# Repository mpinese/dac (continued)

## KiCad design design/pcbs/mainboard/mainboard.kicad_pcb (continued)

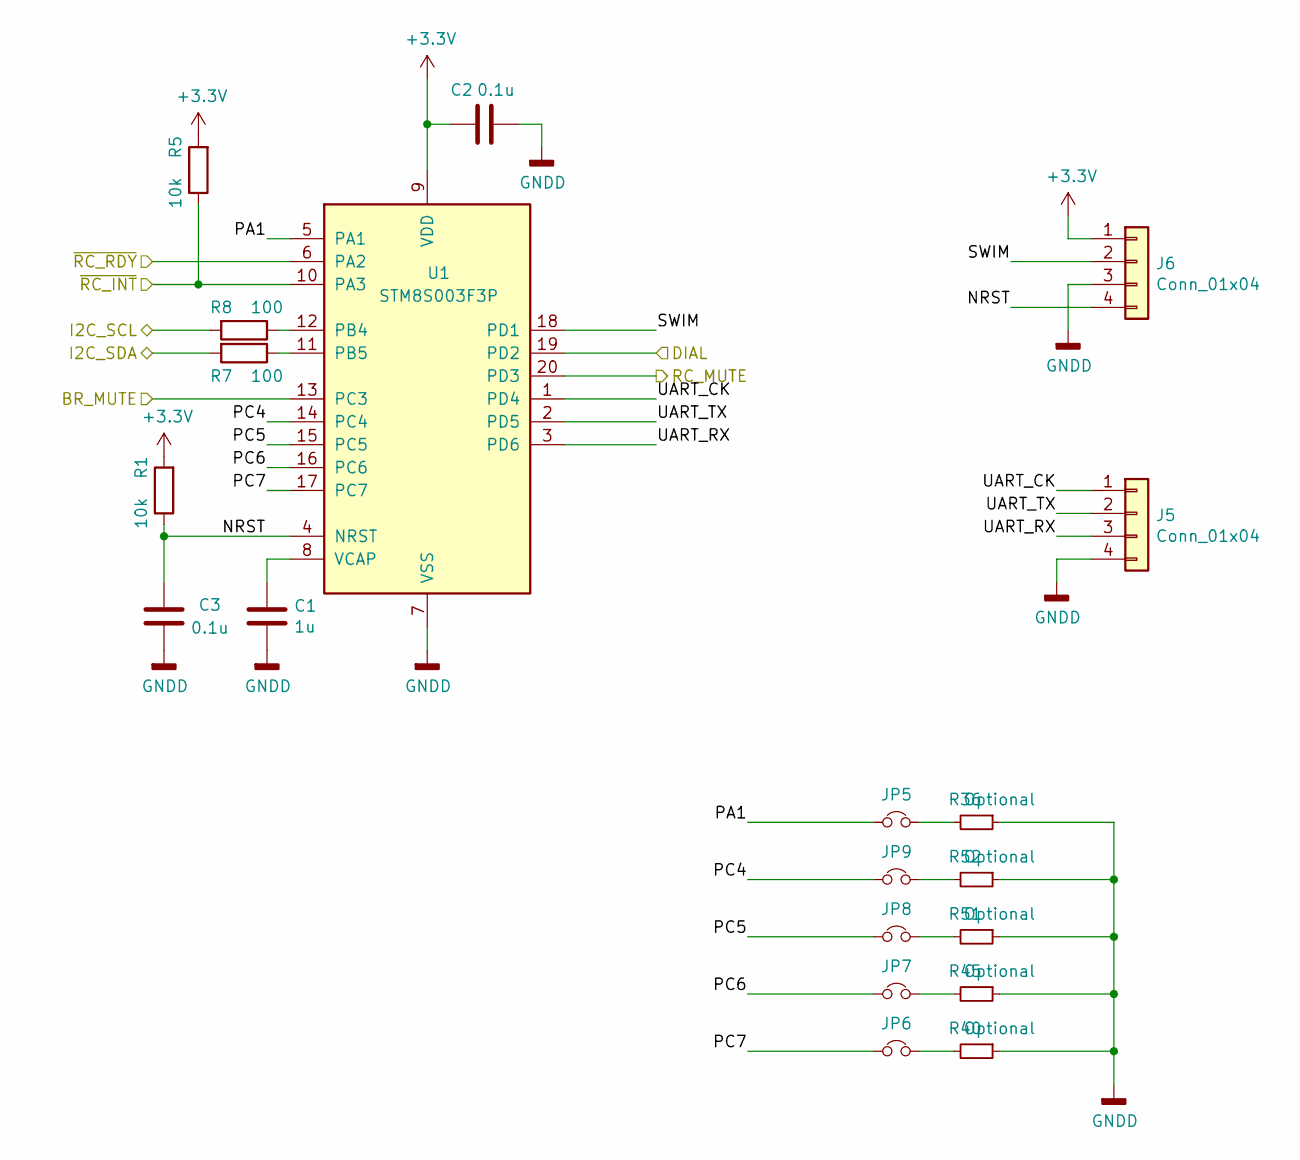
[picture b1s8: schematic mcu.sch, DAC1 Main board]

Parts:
C1: 1u; C_0805_2012Metric; LCSC C28323
C2, C3: 0.1u; C_0603_1608Metric; LCSC C14663
J5, J6: Conn_01x04; PinHeader_1x04_P2.54mm_Vertical
JP5, JP6, JP7, JP8, JP9: PinHeader_1x02_P2.54mm_Vertical
R1, R5: 10k; R_0402_1005Metric; LCSC C25744
R7, R8: 100; R_0402_1005Metric; LCSC C25076
R36, R40, R45, R51, R52: Optional; R_Axial_DIN0204_L3.6mm_D1.6mm_P5.08mm_Horizontal
U1: STM8S003F3P; TSSOP-20_4.4x6.5mm_P0.65mm; LCSC C52717

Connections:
/ASRC/I2C_SCL: R8.2; also elsewhere on the board
/ASRC/I2C_SDA: R7.2; also elsewhere on the board
/ASRC/MUTE: U1.20 (PD3); also elsewhere on the board
/ASRC/~INT: R5.1, U1.10 (PA3); also elsewhere on the board
/MCU/BR_MUTE: U1.13 (PC3); also elsewhere on the board
/MCU/DIAL: U1.19 (PD2); also elsewhere on the board
/MCU/NRST: C3.1, J6.4, R1.1, U1.4 (NRST)
/MCU/PA1: JP5.1, U1.5 (PA1)
/MCU/PC4: JP9.1, U1.14 (PC4)
/MCU/PC5: JP8.1, U1.15 (PC5)
/MCU/PC6: JP7.1, U1.16 (PC6)
/MCU/PC7: JP6.1, U1.17 (PC7)
/MCU/SWIM: J6.2, U1.18 (PD1)
/MCU/UART_CK: J5.1, U1.1 (PD4)
/MCU/UART_RX: J5.3, U1.3 (PD6)
/MCU/UART_TX: J5.2, U1.2 (PD5)
/MCU/~RC_RDY: U1.6 (PA2); also elsewhere on the board
GNDD: C1.2, C2.2, C3.2, J5.4, J6.3, R36.1, R40.1, R45.1, R51.1, R52.1, U1.7 (VSS); also elsewhere on the board
unnamed: C1.1, U1.8 (VCAP)
unnamed: JP5.2, R36.2
unnamed: JP6.2, R40.2
unnamed: JP7.2, R45.2
unnamed: JP8.2, R51.2
unnamed: JP9.2, R52.2
unnamed: R7.1, U1.11 (PB5)
unnamed: R8.1, U1.12 (PB4)

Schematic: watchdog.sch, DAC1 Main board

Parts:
C40, C82: 22u; C_0805_2012Metric; LCSC C45783
D2, D3, D6, D7: 5V6; D_MiniMELF; LCSC C8062
D4, D5: D; D_SOD-123F; LCSC C64898
K3, K4: EC2-12NU; RELAY_EC2-5NU; DigiKey 399-11029-5-ND
Q1, Q2, Q4, Q5, Q6, Q7, Q8, Q9, Q11, Q12: SS8050; SOT-23; LCSC C2150
Q3, Q10: SS8550; SOT-23; LCSC C8542
R11, R13, R72, R74: 2.2k; R_0402_1005Metric; LCSC C25879
R12, R14, R68, R69: 5.6k; R_0402_1005Metric; LCSC C25908
R20, R73: 15k; R_0402_1005Metric; LCSC C25756
R21, R71: 10k; R_0402_1005Metric; LCSC C25744
R31, R63: 22k; R_0402_1005Metric; LCSC C25768

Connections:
+10V: D4.1 (K), K3.1, R11.1, R20.1, R31.2; also elsewhere on the board
+10V_AMP: D5.1 (K), K4.1, R63.2, R73.1, R74.1; also elsewhere on the board
-10V: C40.2, Q2.2 (E), Q4.2 (E), Q5.2 (E), R14.2; also elsewhere on the board
-10V_AMP: C82.2, Q8.2 (E), Q9.2 (E), Q11.2 (E), R68.2; also elsewhere on the board
/Headphone Amp/LOUT: K4.4; also elsewhere on the board
/Headphone Amp/ROUT: K4.9; also elsewhere on the board
/LOUT: K3.4; also elsewhere on the board
/ROUT: K3.9; also elsewhere on the board
GND_AMP: K4.3, K4.10, Q7.2 (E), Q10.1 (B), Q12.2 (E), R69.2, R71.1, R72.1; also elsewhere on the board
unnamed: C40.1, Q4.3 (C), Q5.3 (C), Q6.1 (B), R31.1
unnamed: C82.1, Q7.1 (B), Q8.3 (C), Q9.3 (C), R63.1
unnamed: D2.1 (K), R11.2, R12.1
unnamed: D2.2 (A), Q1.1 (B)
unnamed: D3.1 (K), R13.2, R14.1
unnamed: D3.2 (A), Q2.1 (B)
unnamed: D4.2 (A), K3.12, Q6.3 (C)
unnamed: D5.2 (A), K4.12, Q7.3 (C)
unnamed: D6.1 (K), R68.1, R72.2
unnamed: D6.2 (A), Q11.1 (B)
unnamed: D7.1 (K), R69.1, R74.2
unnamed: D7.2 (A), Q12.1 (B)
unnamed: Q1.3 (C), Q3.2 (E), R20.2
unnamed: Q2.3 (C), Q4.1 (B), R21.2
unnamed: Q3.3 (C), Q5.1 (B)
unnamed: Q10.2 (E), Q12.3 (C), R73.2
unnamed: Q8.1 (B), Q10.3 (C)
unnamed: Q9.1 (B), Q11.3 (C), R71.2

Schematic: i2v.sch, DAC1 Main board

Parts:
C23, C36, C50, C52, C62, C70: 10u; CP_EIA-3216-18_Kemet-A; LCSC C7171
C24, C47, C53, C69: 430p; C_0603_1608Metric; DigiKey 399-15401-1-ND
C26, C41, C46, C57, C58, C68: 0.1u; C_0603_1608Metric; LCSC C14663
C37, C38, C65, C66: 1.2n; C_0603_1608Metric; DigiKey 399-14950-1-ND
R27, R35, R43, R53: 820; R_0603_1608Metric; DigiKey RG16N820WCT-ND
R28, R30, R48, R50: 1k; R_0603_1608Metric; DigiKey RG16N1.0KWCT-ND
R33, R34, R46, R47: 270; R_0603_1608Metric; DigiKey RG16N270WCT-ND
R38, R42: 25; R_0603_1608Metric; DigiKey 764-1409-1-ND
U9, U13, U15: OPA1612AxD; SOIC-8_3.9x4.9mm_P1.27mm; DigiKey 296-39098-1-ND

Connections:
+10V: C23.1, C26.1, C36.1, C46.1, C52.1, C58.1, U9.8 (V+), U13.8 (V+), U15.8 (V+); also elsewhere on the board
-10V: C41.2, C50.2, C57.2, C62.2, C68.2, C70.2, U9.4 (V-), U13.4 (V-), U15.4 (V-); also elsewhere on the board
/DAC/I2V/IIN+L: C53.1, R43.2, U15.6 (-); also elsewhere on the board
/DAC/I2V/IIN+R: C24.1, R27.2, U9.6 (-); also elsewhere on the board
/DAC/I2V/IIN-L: C69.1, R53.2, U15.2 (-); also elsewhere on the board
/DAC/I2V/IIN-R: C47.1, R35.2, U9.2 (-); also elsewhere on the board
/LOUT: R42.1; also elsewhere on the board
/ROUT: R38.1; also elsewhere on the board
unnamed: C24.2, R27.1, R28.2, U9.7
unnamed: C37.1, R33.2, R38.2, U13.7
unnamed: C37.2, R30.1, R33.1, U13.6 (-)
unnamed: C38.1, R28.1, R34.2, U13.5 (+)
unnamed: C47.2, R30.2, R35.1, U9.1
unnamed: C53.2, R43.1, R48.2, U15.7
unnamed: C65.1, R42.2, R46.2, U13.1
unnamed: C65.2, R46.1, R50.1, U13.2 (-)
unnamed: C66.1, R47.2, R48.1, U13.3 (+)
unnamed: C69.2, R50.2, R53.1, U15.1

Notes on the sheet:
Equations defining behaviour: R1: TIA feedback R2: DA series R3: DA feedback C1: TIA feedback C3: DA feedback (1) R1*(6.2+7.8/2)*1e-3 <= 10-1 (1 V headroom w/ 10 V rail) (2) R3/R2*R1*7.8*1e-3 <= 3.472/2 (Line out level) (3) R3/R2 is minimised (Minimise noise gain) (4) 3.472 - R3/R2*R1*7.8*1e-3 is m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
TINA-TI simulations:
Phase margin 57 deg @ 37 MHz:
Group delay flat to 20 kHz:
Gain flat to 20 kHz:
Noise 700 nV RMS up to 20 kHz
In THD+N terms this noise is 0.000057% relative to a 1.228 V RMS full scale.

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
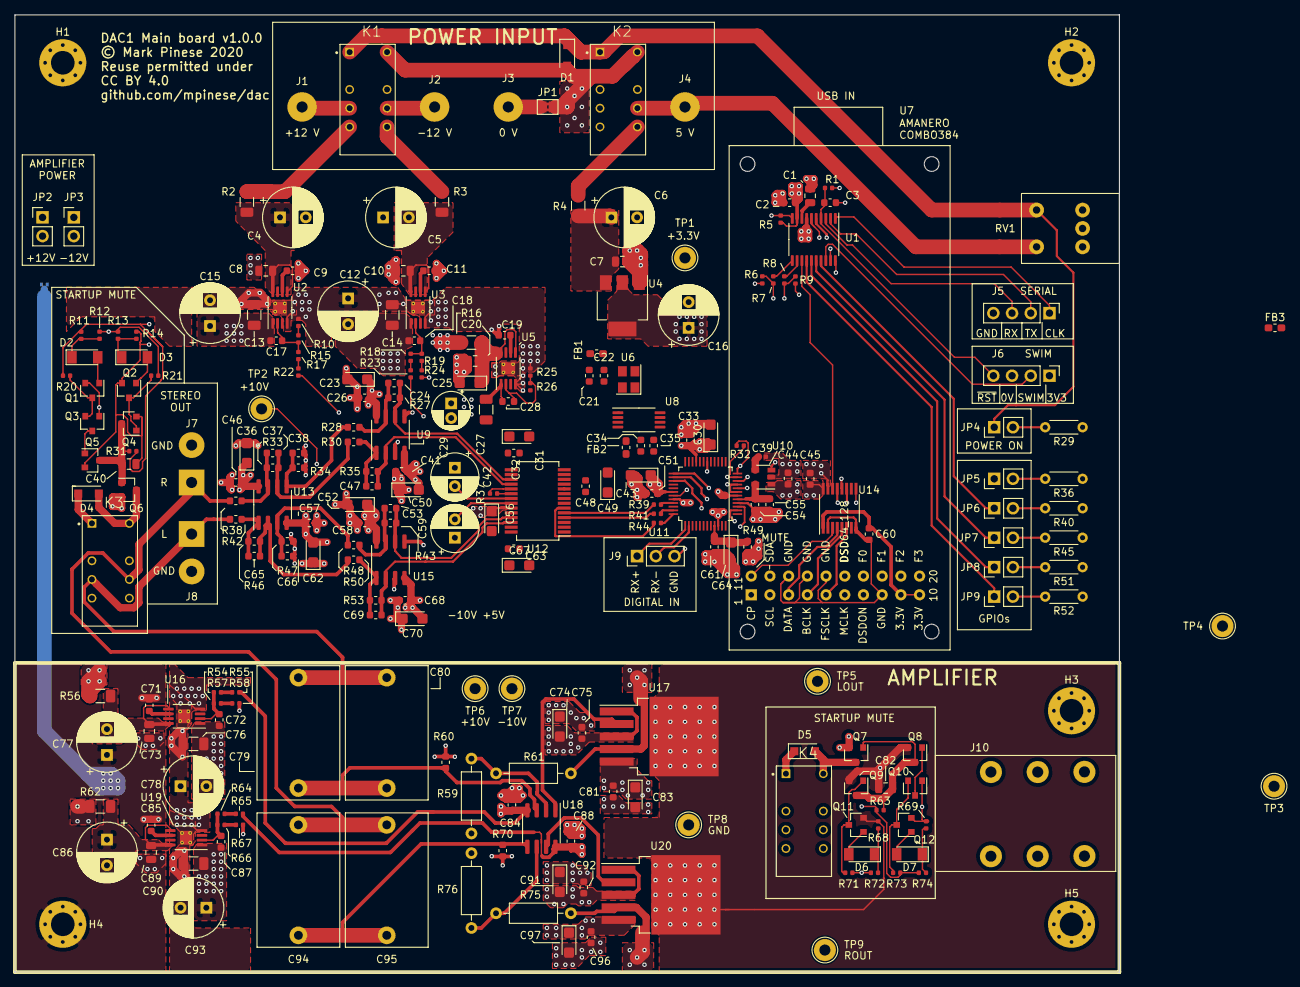
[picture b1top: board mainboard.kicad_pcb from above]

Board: 4 copper layers, 150.0 x 130.0 mm, 254 parts (1 on the bottom side), 139 nets.

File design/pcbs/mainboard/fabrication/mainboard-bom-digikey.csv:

Comment,Designator,Footprint,DigiKey,Quantity
KC3225K24.5760C1GE00,U6,Crystal:Crystal_SMD_3225-4Pin_3.2x2.5mm,1253-1407-1-ND,1
100u,C16,Capacitor_THT:CP_Radial_D8.0mm_P3.50mm,1572-1662-ND,1
TPS79318-EP,U10,Package_TO_SOT_SMD:SOT-23-5,296-12155-1-ND,1
SRC4392,U11,Package_QFP:TQFP-48_7x7mm_P0.5mm,296-19740-1-ND,1
PCM1792A,U12,Package_SO:SSOP-28_5.3x10.2mm_P0.65mm,296-26303-5-ND,1
TPS7A30,"U3,U16",Package_SO:MSOP-8-1EP_3x3mm_P0.65mm_EP1.68x1.88mm_ThermalVias,296-27750-1-ND,2
TPS7A49,"U2,U19,U5",Package_SO:MSOP-8-1EP_3x3mm_P0.65mm_EP1.68x1.88mm_ThermalVias,296-27751-1-ND,3
TLV1117-33,U4,Package_TO_SOT_SMD:SOT-223-3_TabPin2,296-28778-1-ND,1
OPA1612AxD,"U18,U15,U9,U13",Package_SO:SOIC-8_3.9x4.9mm_P1.27mm,296-39098-1-ND,4
LME49600,"U17,U20",Package_TO_SOT_SMD:TO-263-5_TabPin3,296-43968-5-ND,2
Si8645BA-B-IU,U14,Package_SO:QSOP-16_3.9x4.9mm_P0.635mm,336-2096-5-ND,1
EC2-12NU,"K3,K4",RELAY_EC2-5NU,399-11029-5-ND,2
EC2-5NU,"K1,K2",mainboard:RELAY_EC2-5NU,399-11052-5-ND,2
1.2n,"C37,C38,C65,C66",Capacitor_SMD:C_0603_1608Metric,399-14950-1-ND,4
430p,"C47,C24,C69,C53",Capacitor_SMD:C_0603_1608Metric,399-15401-1-ND,4
4.7,R49,Resistor_SMD:R_0603_1608Metric,408-1436-1-ND,1
2.2u,"C80,C79,C94,C95",Capacitor_THT:C_Rect_L18.0mm_W11.0mm_P15.00mm_FKS3_FKP3,732-11840-ND,4
47u,"C15,C12,C4,C5,C93,C78,C86,C77,C6",Capacitor_THT:CP_Radial_D8.0mm_P3.50mm,732-6324-1-ND,9
47u,"C42,C59,C29",Capacitor_THT:CP_Radial_D5.0mm_P2.00mm,732-9306-1-ND,3
25,"R38,R42",Resistor_SMD:R_0603_1608Metric,764-1409-1-ND,2
5PB1102,U8,Package_SO:TSSOP-8_4.4x3mm_P0.65mm,800-2889-5-ND,1
AudioJackSw,J10,mainboard:Amphenol_ACJS-MHOM,889-1818-ND,1
P091S-FC20BR10K,RV1,mainboard:P091S-FC20BR10K,987-1283-ND,1
1k,"R30,R28,R50,R48",Resistor_SMD:R_0603_1608Metric,RG16N1.0KWCT-ND,4
270,"R33,R34,R46,R47",Resistor_SMD:R_0603_1608Metric,RG16N270WCT-ND,4
820,"R35,R27,R53,R43",Resistor_SMD:R_0603_1608Metric,RG16N820WCT-ND,4
4.7k,"R60,R70",Resistor_SMD:R_0603_1608Metric,RG16P4.7KBCT-ND,2
Conn_Coaxial,"J7,J8",Connector_Wire:SolderWirePad_1x02_P5.08mm_Drill1.5mm,SC1828-ND,2
XLR5,#J3,,IO-XLR5-M-EV,1

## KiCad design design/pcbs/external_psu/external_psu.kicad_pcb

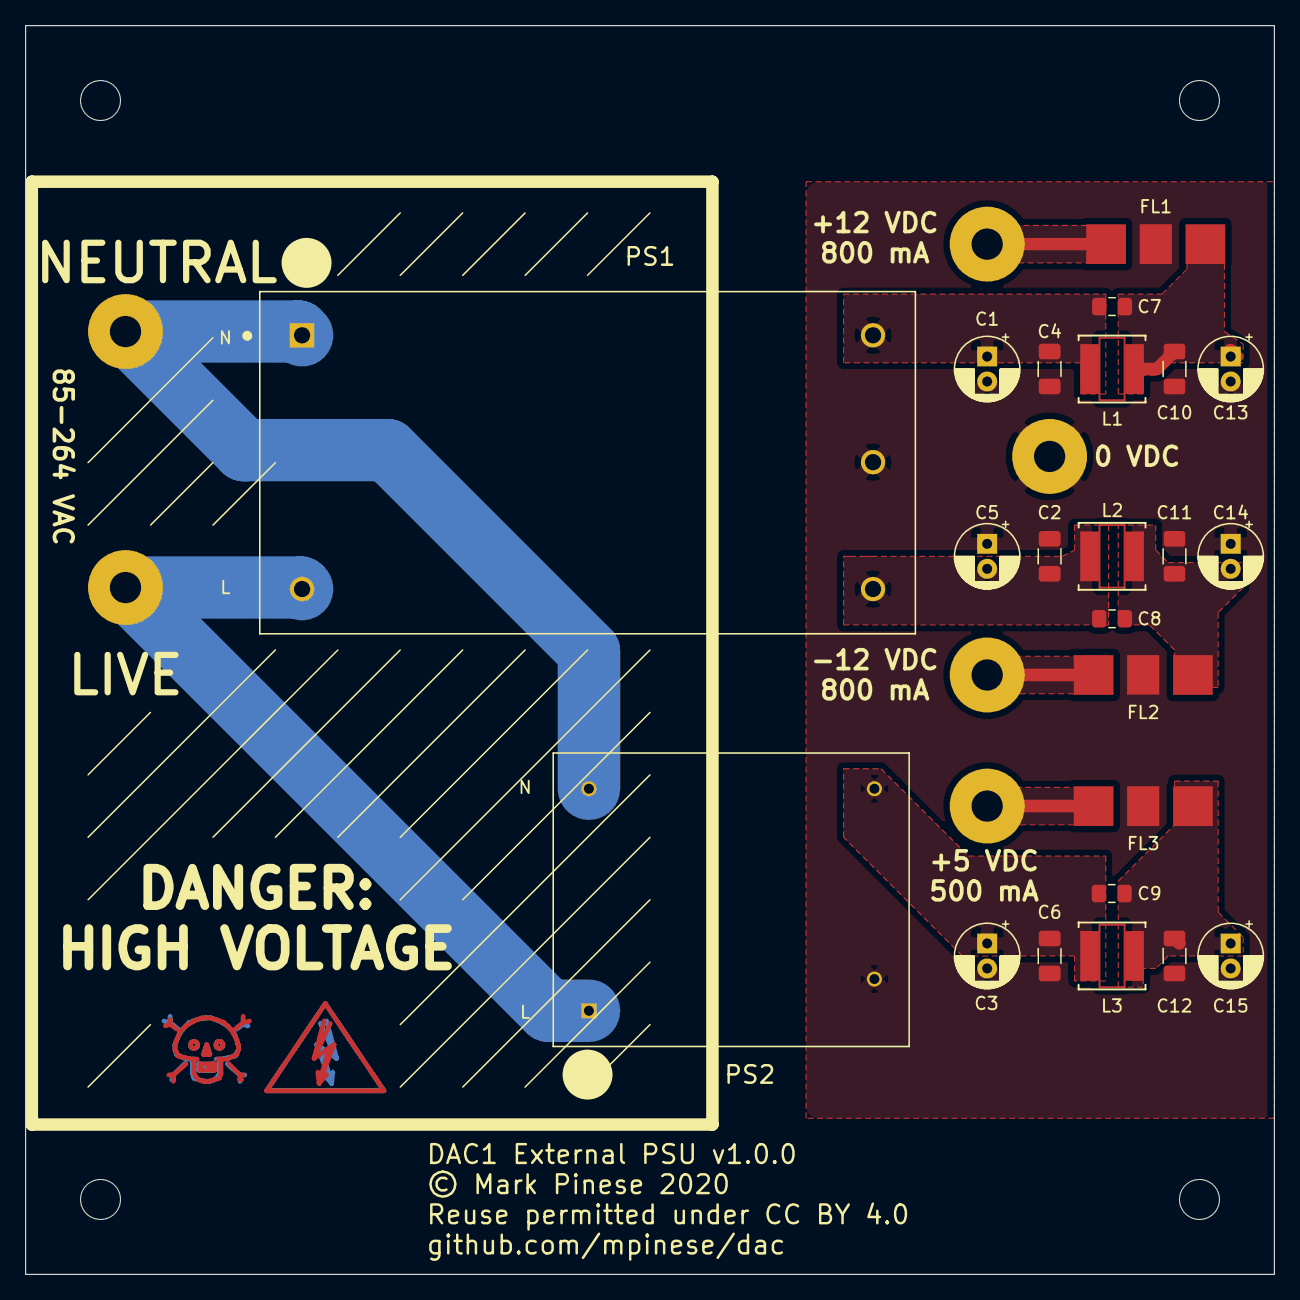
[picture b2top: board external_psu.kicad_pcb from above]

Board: 2 copper layers, 100.0 x 100.0 mm, 33 parts (0 on the bottom side), 12 nets.

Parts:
C1, C2, C3, C13, C14, C15: 6.8u; CP_Radial_D5.0mm_P2.00mm
C4, C5, C6, C10, C11, C12: 2.2u; C_1206_3216Metric
C7, C8, C9: 15n; C_0805_2012Metric_Pad1.15x1.40mm_HandSolder
CONN1: L; SolderWirePad_1x01_Drill2.5mm
CONN2: N; SolderWirePad_1x01_Drill2.5mm
CONN3: +12V; SolderWirePad_1x01_Drill2.5mm
CONN4: 0V; SolderWirePad_1x01_Drill2.5mm
CONN5: -12V; SolderWirePad_1x01_Drill2.5mm
CONN6: +5V; SolderWirePad_1x01_Drill2.5mm
FL1, FL2, FL3: EMI_Filter_CLC; 4700-008MLF
H1, H2, H3, H4: MountingHole; MountingHole_3.2mm_M3
L1, L2, L3: 15u; NRS5020T150MMGJ
PS1: RAC20-12DK; CONV_RAC20-12DK
PS2: RAC03-05SK; CONV_RAC03-05SK

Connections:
/LIVE: CONN1.1, PS1.2, PS2.1
/NEUTRAL: CONN2.1, PS1.1, PS2.4
GND: C1.2, C2.1, C3.2, C4.2, C5.2, C6.2, C10.2, C11.2, C12.2, C13.2, C14.1, C15.2, CONN4.1, FL1.2, FL2.2, FL3.2, PS1.4, PS2.2
unnamed: C1.1, C4.1, C7.1, L1.1, PS1.5
unnamed: C2.2, C5.1, C8.1, L2.1, PS1.3
unnamed: C3.1, C6.1, C9.1, L3.1, PS2.3
unnamed: C7.2, C10.1, C13.1, FL1.1, L1.2
unnamed: C8.2, C11.1, C14.2, FL2.1, L2.2
unnamed: C9.2, C12.1, C15.1, FL3.1, L3.2
unnamed: CONN3.1, FL1.3
unnamed: CONN5.1, FL2.3
unnamed: CONN6.1, FL3.3

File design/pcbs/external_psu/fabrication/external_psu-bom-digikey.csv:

Comment,Designator,Footprint, DigiKey,Quantity
6.8u,"C1,C13,C2,C14,C3,C15",Capacitor_THT:CP_Radial_D5.0mm_P2.00mm,565-4006-ND,6
2.2u,"C4,C10,C5,C11,C6,C12",Capacitor_SMD:C_1206_3216Metric,1276-3137-1-ND,6
15n,"C7,C8,C9",Capacitor_SMD:C_0805_2012Metric_Pad1.15x1.40mm_HandSolder,732-12189-1-ND,3
~,#FB1,,240-2497-ND,1
EMI_Filter_CLC,"FL1,FL2,FL3",dac:4700-008MLF,410-1196-1-ND,3
15u,"L1,L2,L3",dac:NRS5020T150MMGJ,587-2410-1-ND,3
RAC20-12DK,PS1,CONV_RAC20-12DK,945-3239-ND,1
RAC03-05SK,PS2,CONV_RAC03-05SK,945-3441-ND,1
IEC 320-C14 socket,#J1,,Q334-ND ,1
XLR5,#J2,,1937-1035-ND,1

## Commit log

2020-06-25 Initial commit.
2020-06-27 Added jitter simulation that supports the use of a 5 ps RMS jitter oscillator.
2020-06-27 Completed layout of main board, cleaned up some libraries.
2020-06-27 Fixed mounting hole alignment
2020-06-27 Tweaked silkscreen to better identify optional modules.
2020-06-27 Renumbered footprints to follow board position.
2020-06-27 Fixed PCB 3D models.
2020-06-27 Silkscreen tweaks
2020-06-27 Updated PCB sheet info. Clarified licence in readme.
2020-06-27 Removed outdated files.
2020-06-27 Removed tracking of Kicad -bak files.
2020-06-28 Fixed title blocks. Added fab outputs.
2020-09-04 Misc updates
2020-09-04 Added note about work in progress.
